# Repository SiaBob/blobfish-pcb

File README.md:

# blobfish-pcb
My first PCB for solder hack club

# Schematic

# PCB

# Features
Sr latch that turns on the blobfish's eyes

# BOM
1 Battery holder, 
4 NPN Transistor, 
4 4.7k Resistor, 
3 220 Resistor, 
2 Push Button,

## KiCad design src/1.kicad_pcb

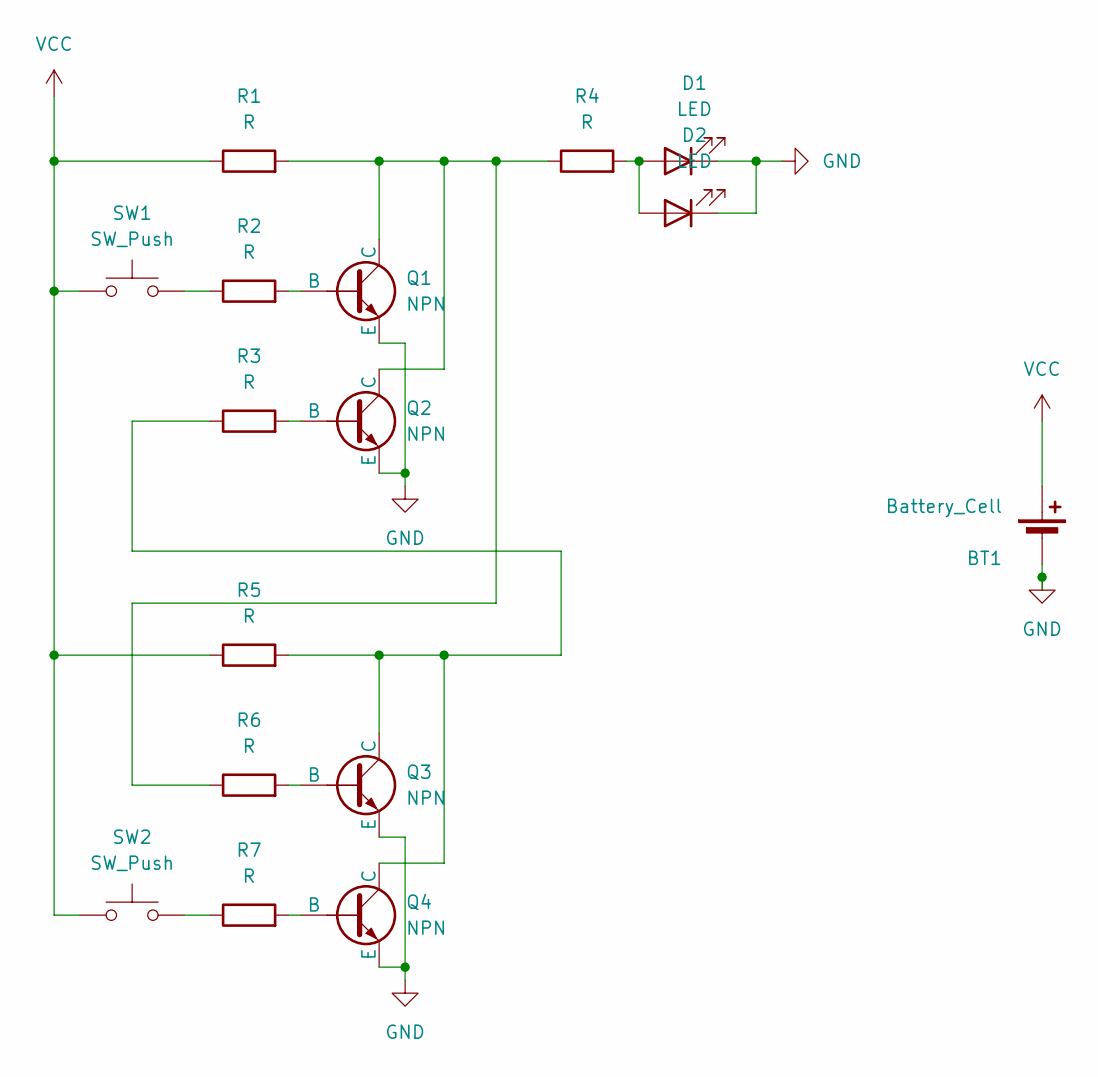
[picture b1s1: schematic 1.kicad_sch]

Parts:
BT1: Battery_Cell; BatteryHolder_Keystone_3034_1x20mm
D1, D2: LED; LED_D5.0mm
Q1, Q2, Q3, Q4: NPN; TO-92L_HandSolder
R1, R2, R3, R4, R5, R6, R7: R; R_Axial_DIN0207_L6.3mm_D2.5mm_P7.62mm_Horizontal
SW1, SW2: SW_Push; SW_PUSH_6mm

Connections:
GND: BT1.2 (-), D1.1 (K), D2.1 (K), Q1.3 (E), Q2.3 (E), Q3.3 (E), Q4.3 (E)
unnamed: D1.2 (A), D2.2 (A), R4.2
unnamed: Q1.2 (B), R2.2
unnamed: Q1.1 (C), Q2.1 (C), R1.2, R4.1, R6.1
unnamed: Q2.2 (B), R3.2
unnamed: Q3.2 (B), R6.2
unnamed: Q3.1 (C), Q4.1 (C), R3.1, R5.2
unnamed: Q4.2 (B), R7.2
unnamed: R2.1, SW1.2
unnamed: R7.1, SW2.2
VCC: BT1.1 (+), R1.1, R5.1, SW1.1, SW2.1

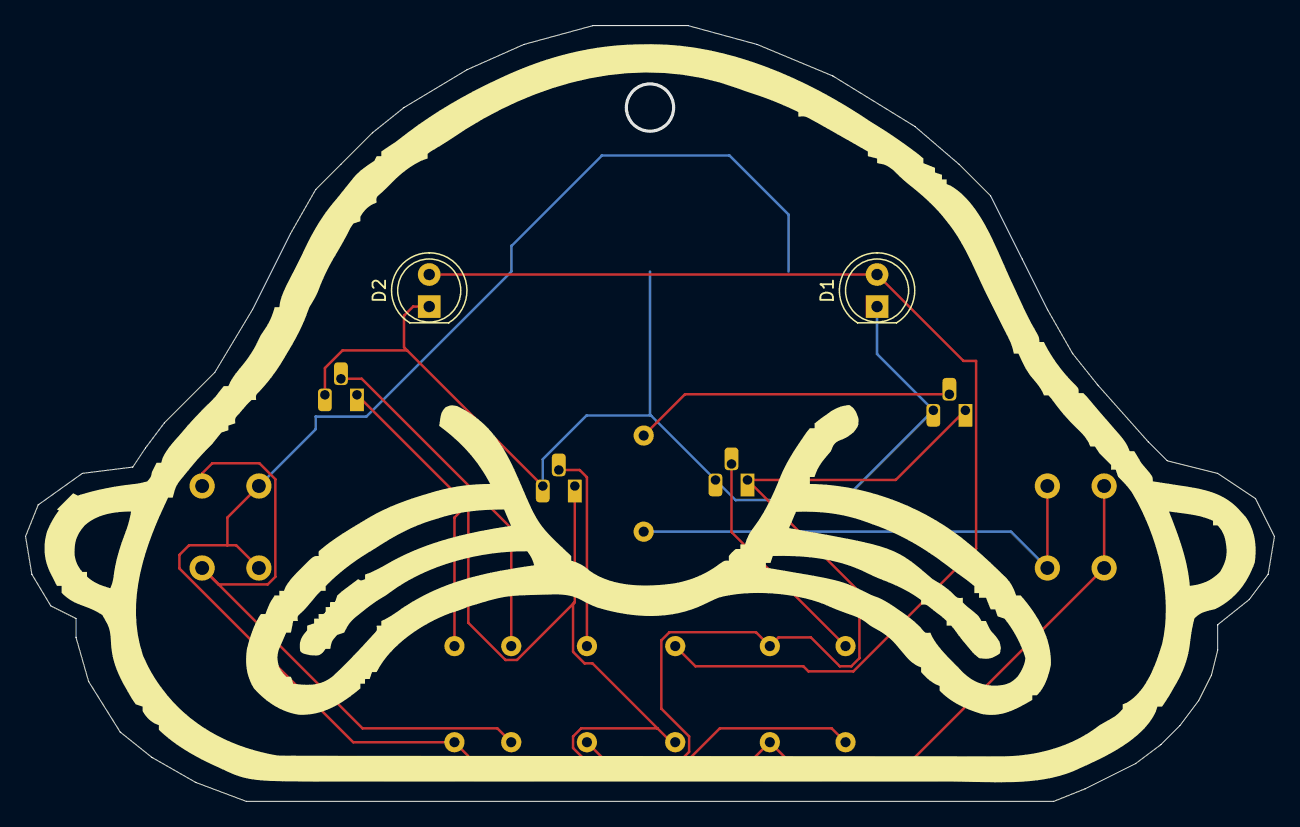
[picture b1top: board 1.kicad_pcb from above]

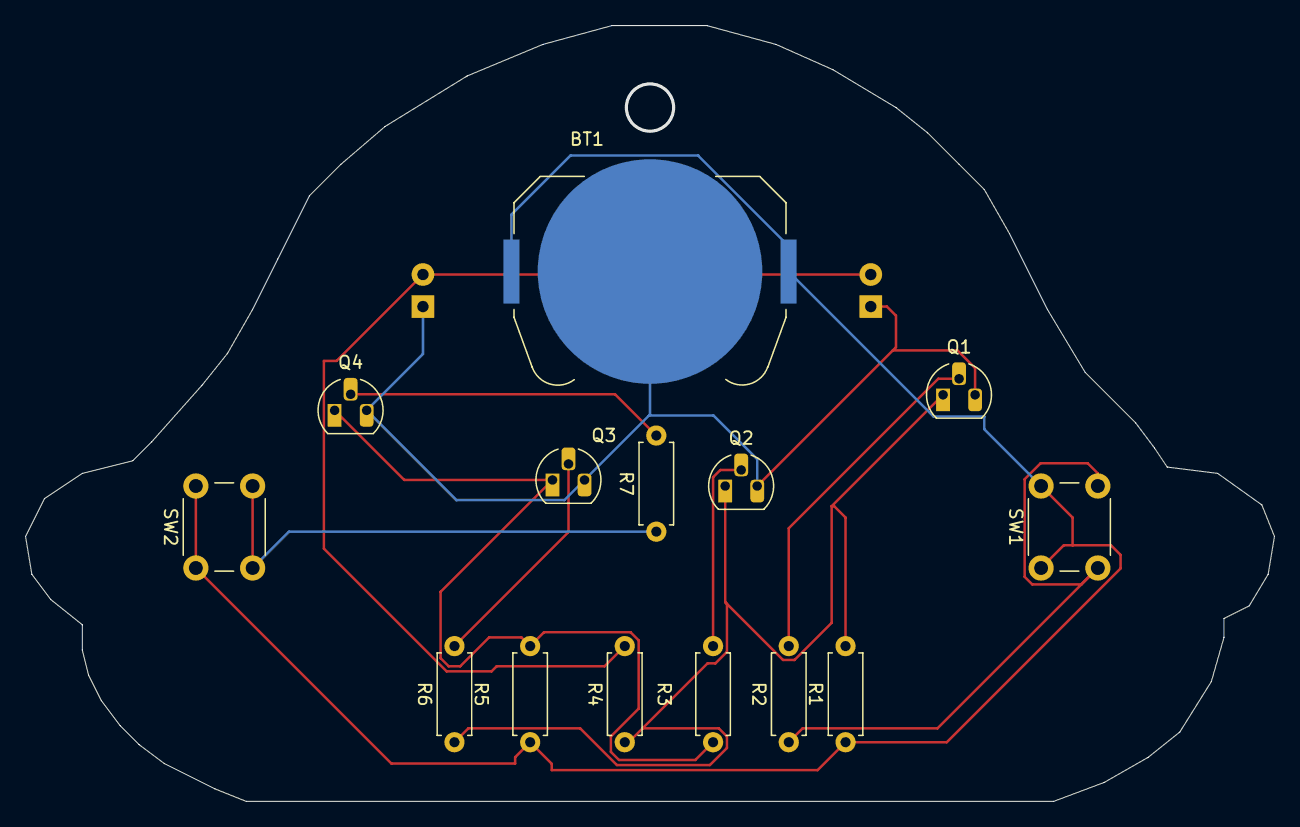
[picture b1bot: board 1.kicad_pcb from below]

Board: 2 copper layers, 99.0 x 61.5 mm, 16 parts (14 on the bottom side), 11 nets.

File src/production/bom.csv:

Designator,Footprint,Quantity,Value,LCSC Part #
BT1,BatteryHolder_Keystone_3034_1x20mm,1,Battery_Cell,
"D1, D2",LED_D5.0mm,2,LED,
"Q1, Q2, Q3, Q4",TO-92L_HandSolder,4,NPN,
"R1, R2, R3, R4, R5, R6, R7",R_Axial_DIN0207_L6.3mm_D2.5mm_P7.62mm_Horizontal,7,R,
"SW1, SW2",SW_PUSH_6mm,2,SW_Push,

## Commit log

2025-06-13 file
